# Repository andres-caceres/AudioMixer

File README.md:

# AudioMixer v1.2 (beta)
Digital audio USB controller firmware for Windows, tested using an Arduino Nano. Lets you control the volume of different applications using potentiometers and mute each channel individually using push button switches.
Based on [Deej by Omriharel], can be used with deej.exe Windows client.

## Features
* Includes mute push button functionality and ADC range calibration settings for each channel.
* Supports TM1637 7 segment display for controller position feedback.
* Supports LED push buttons for visual feedback.
* Uses digital filtering to increase potentiometer position accuracy.

## Upcoming (desired) Features
* Windows audio device selection using one push button press.
* Push buttons that can be used for executing Macros to automate tasks.
* Calibration subroutine for sliders

(Work in progress)

[//]: #

[Deej by Omriharel]: <https://github.com/omriharel/deej>

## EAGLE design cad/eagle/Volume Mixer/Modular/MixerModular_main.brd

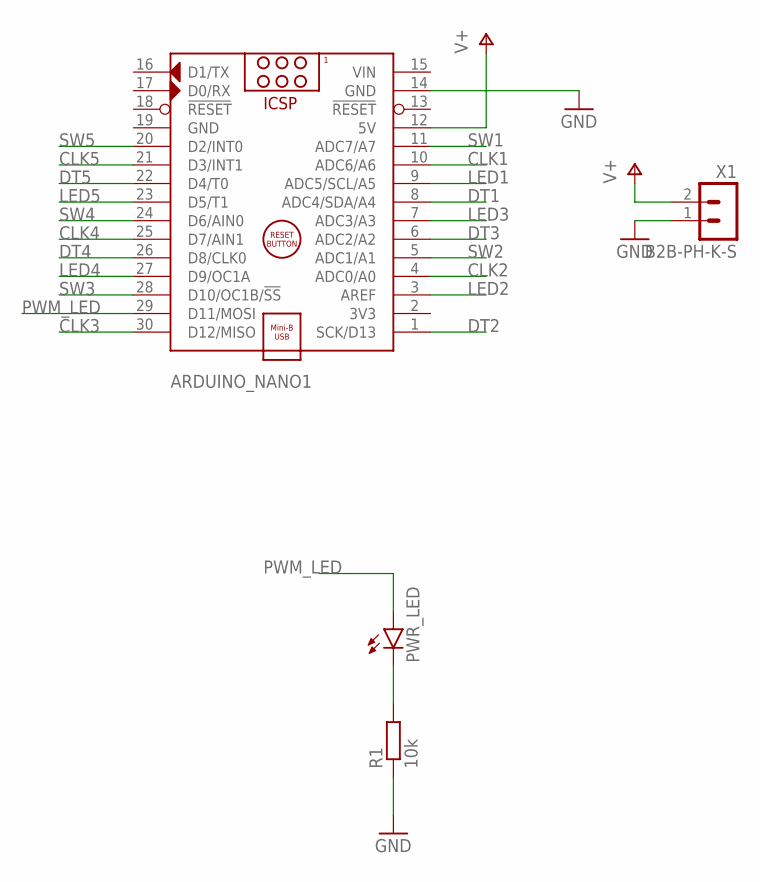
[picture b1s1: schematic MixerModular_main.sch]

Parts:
ARDUINO_NANO1: ARDUINO_NANO
PWR_LED: LED5MM
R1: 10k; 0207/10
X1: B2B-PH-K-S

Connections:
CLK1: ARDUINO_NANO1.10 (ADC6/A6)
CLK2: ARDUINO_NANO1.4 (ADC0/A0)
CLK3: ARDUINO_NANO1.30 (D12/MISO)
CLK4: ARDUINO_NANO1.25 (D7/AIN1)
CLK5: ARDUINO_NANO1.21 (D3/INT1)
DT1: ARDUINO_NANO1.8 (ADC4/SDA/A4)
DT2: ARDUINO_NANO1.1 (SCK/D13)
DT3: ARDUINO_NANO1.6 (ADC2/A2)
DT4: ARDUINO_NANO1.26 (D8/CLK0)
DT5: ARDUINO_NANO1.22 (D4/T0)
GND: ARDUINO_NANO1.14 (GND), ARDUINO_NANO1.19 (GND), R1.1, X1.1
LED1: ARDUINO_NANO1.9 (ADC5/SCL/A5)
LED2: ARDUINO_NANO1.3 (AREF)
LED3: ARDUINO_NANO1.7 (ADC3/A3)
LED4: ARDUINO_NANO1.27 (D9/OC1A)
LED5: ARDUINO_NANO1.23 (D5/T1)
unnamed: PWR_LED.K (C), R1.2
PWM_LED: ARDUINO_NANO1.29 (D11/MOSI), PWR_LED.A
SW1: ARDUINO_NANO1.11 (ADC7/A7)
SW2: ARDUINO_NANO1.5 (ADC1/A1)
SW3: ARDUINO_NANO1.28 (D10/OC1B/!SS)
SW4: ARDUINO_NANO1.24 (D6/AIN0)
SW5: ARDUINO_NANO1.20 (D2/INT0)
V+: ARDUINO_NANO1.12 (5V), X1.2
VIN: ARDUINO_NANO1.15 (VIN)

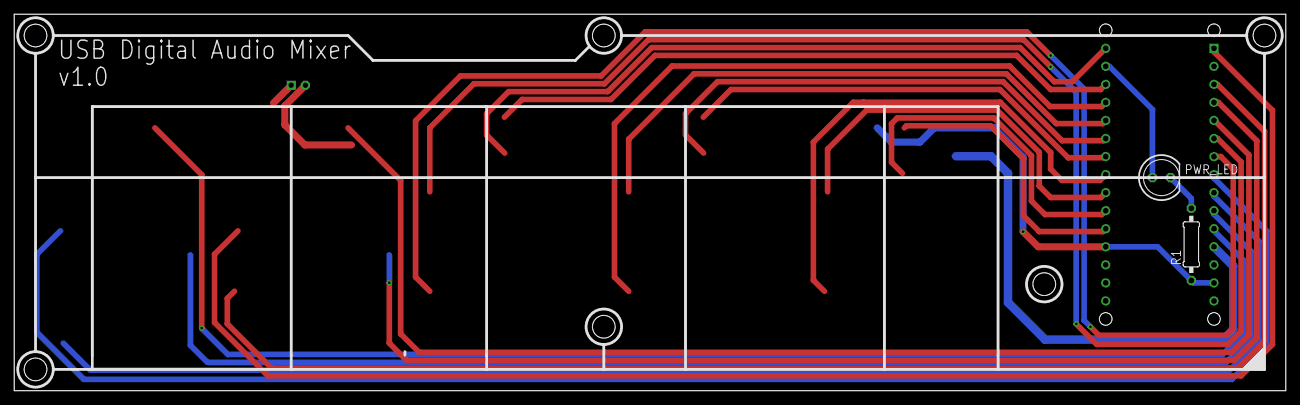
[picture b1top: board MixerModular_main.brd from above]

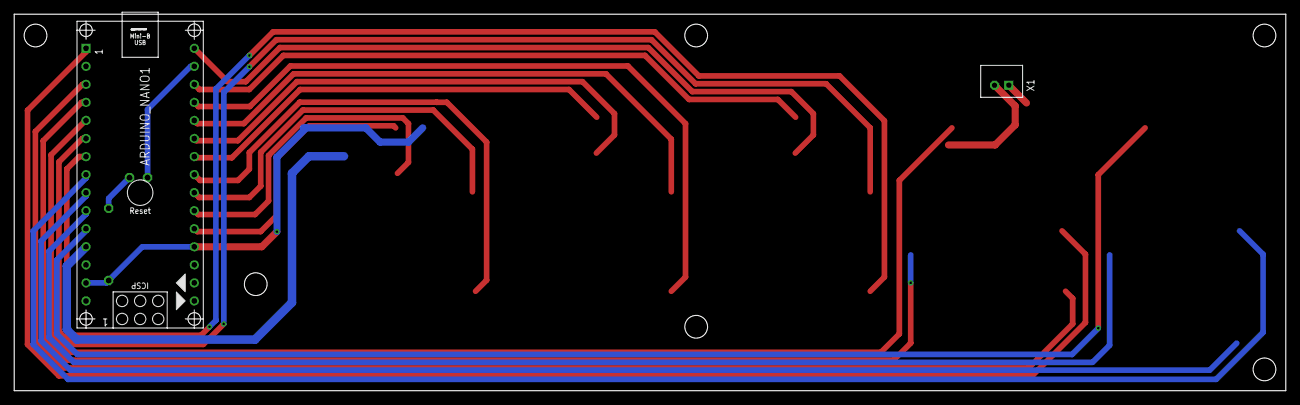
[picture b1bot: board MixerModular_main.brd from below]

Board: 2 copper layers, 179.0 x 53.0 mm, 4 parts (2 on the bottom side), 4 nets.

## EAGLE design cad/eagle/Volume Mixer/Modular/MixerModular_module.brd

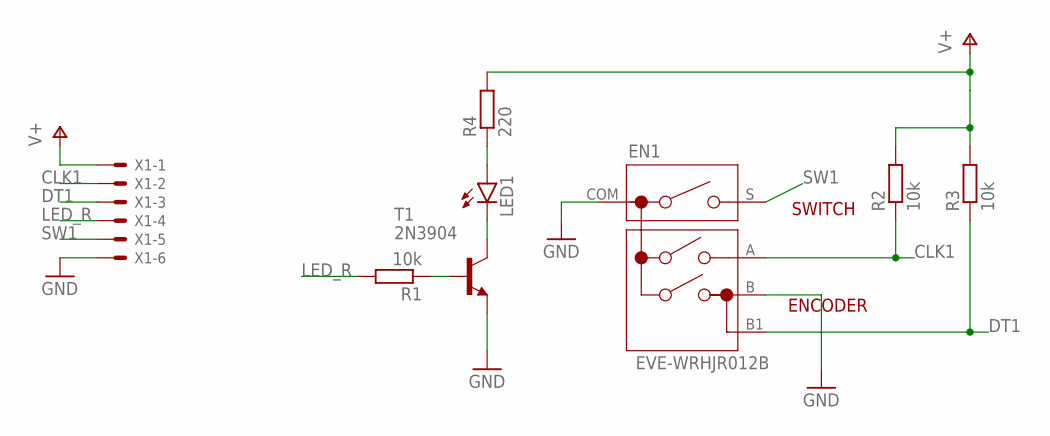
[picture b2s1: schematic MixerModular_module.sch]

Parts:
EN1: EVE-WRHJR012B
LED1: LED5MM
R1, R2, R3: 10k; 0207/10
R4: 220; 0207/10
T1: 2N3904; TO92
X1: 22-23-2061

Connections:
CLK1: EN1.A, R2.1, X1.2
DT1: EN1.B1, R3.1, X1.3
GND: EN1.B, EN1.COM, T1.3 (E), X1.6
LED_R: R1.2, X1.4
unnamed: LED1.A, R4.1
unnamed: R1.1, T1.2 (B)
unnamed: LED1.K (C), T1.1 (C)
SW1: EN1.S, X1.5
V+: R2.2, R3.2, R4.2, X1.1

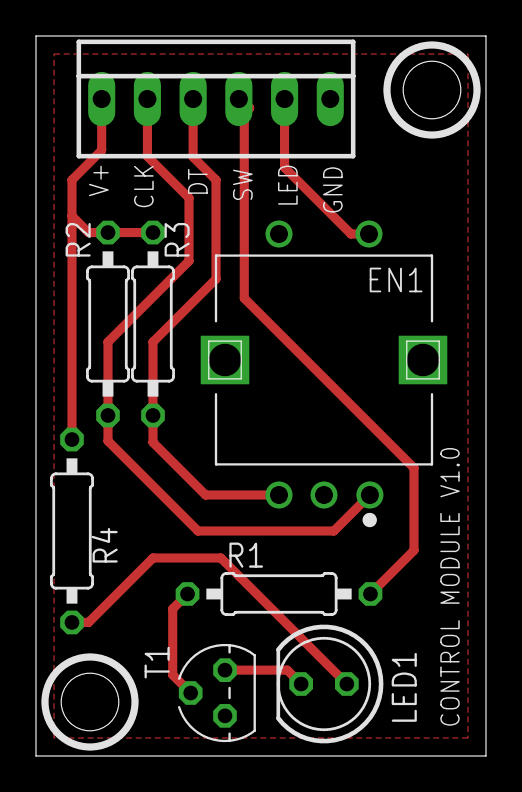
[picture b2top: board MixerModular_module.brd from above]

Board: 2 copper layers, 25.0 x 40.0 mm, 8 parts (0 on the bottom side), 9 nets.

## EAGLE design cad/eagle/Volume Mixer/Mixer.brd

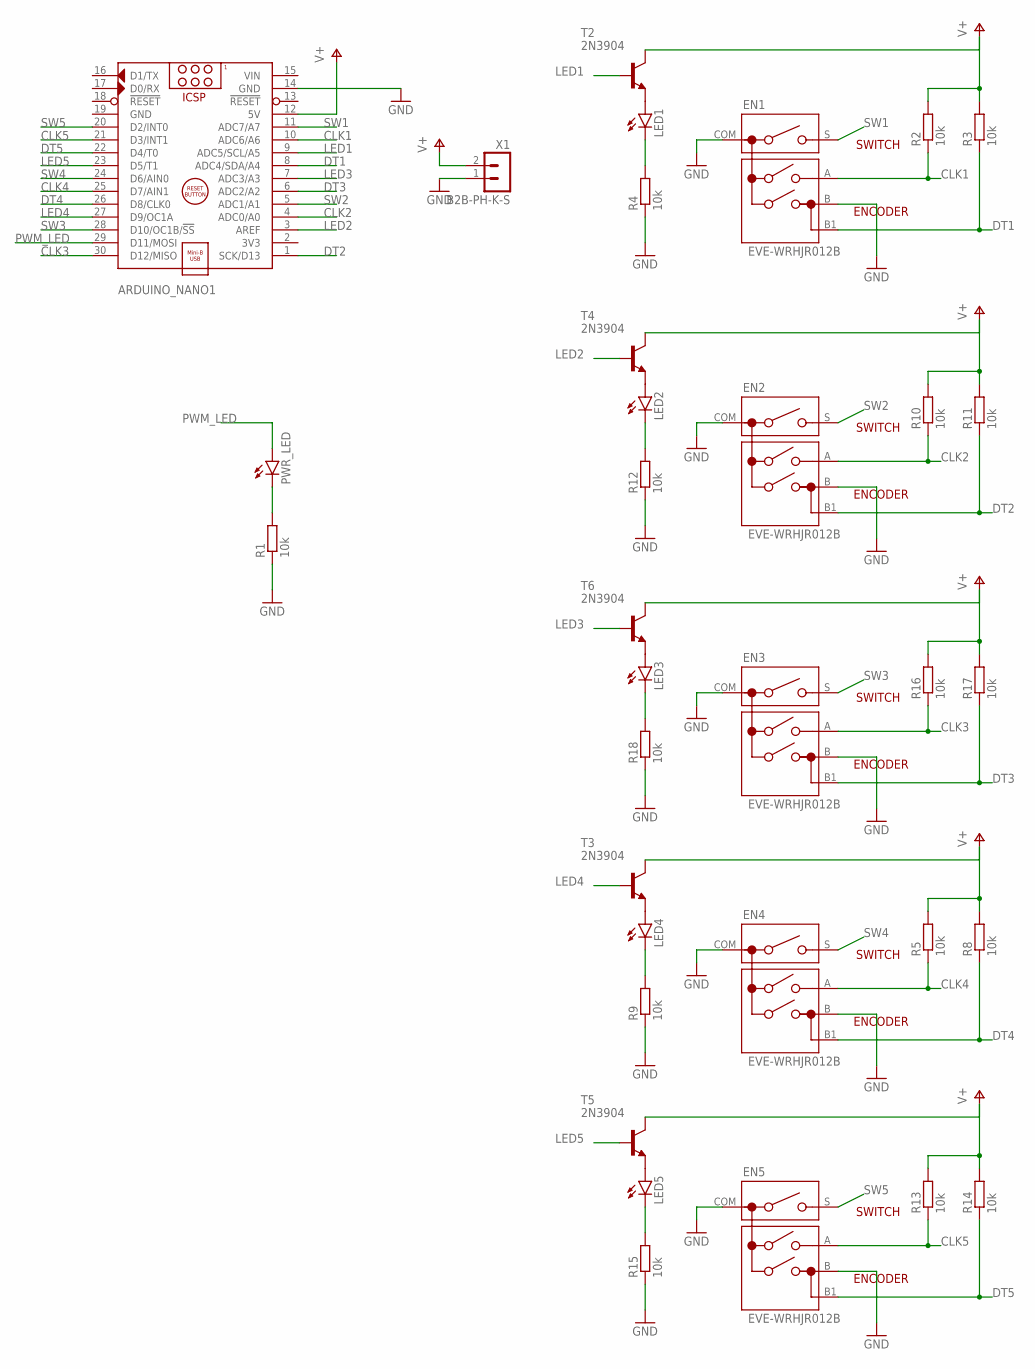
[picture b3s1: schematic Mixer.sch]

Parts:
ARDUINO_NANO1: ARDUINO_NANO
EN1, EN2, EN3, EN4, EN5: EVE-WRHJR012B
LED1, LED2, LED3, LED4, LED5: LED5MM
PWR_LED: LED5MM
R1, R2, R3, R4, R5, R8, R9, R10, R11, R12, R13, R14, R15, R16, R17, R18: 10k; 0207/10
T2, T3, T4, T5, T6: 2N3904; TO92
X1: B2B-PH-K-S

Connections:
CLK1: ARDUINO_NANO1.10 (ADC6/A6), EN1.A, R2.1
CLK2: ARDUINO_NANO1.4 (ADC0/A0), EN2.A, R10.1
CLK3: ARDUINO_NANO1.30 (D12/MISO), EN3.A, R16.1
CLK4: ARDUINO_NANO1.25 (D7/AIN1), EN4.A, R5.1
CLK5: ARDUINO_NANO1.21 (D3/INT1), EN5.A, R13.1
DT1: ARDUINO_NANO1.8 (ADC4/SDA/A4), EN1.B1, R3.1
DT2: ARDUINO_NANO1.1 (SCK/D13), EN2.B1, R11.1
DT3: ARDUINO_NANO1.6 (ADC2/A2), EN3.B1, R17.1
DT4: ARDUINO_NANO1.26 (D8/CLK0), EN4.B1, R8.1
DT5: ARDUINO_NANO1.22 (D4/T0), EN5.B1, R14.1
GND: ARDUINO_NANO1.14 (GND), ARDUINO_NANO1.19 (GND), EN1.B, EN1.COM, EN2.B, EN2.COM, EN3.B, EN3.COM, EN4.B, EN4.COM, EN5.B, EN5.COM, R1.1, R4.1, R9.1, R12.1, R15.1, R18.1, X1.1
LED1: ARDUINO_NANO1.9 (ADC5/SCL/A5), T2.2 (B)
LED2: ARDUINO_NANO1.3 (AREF), T4.2 (B)
LED3: ARDUINO_NANO1.7 (ADC3/A3), T6.2 (B)
LED4: ARDUINO_NANO1.27 (D9/OC1A), T3.2 (B)
LED5: ARDUINO_NANO1.23 (D5/T1), T5.2 (B)
unnamed: PWR_LED.K (C), R1.2
unnamed: LED1.K (C), R4.2
unnamed: LED1.A, T2.3 (E)
unnamed: LED4.K (C), R9.2
unnamed: LED4.A, T3.3 (E)
unnamed: LED2.K (C), R12.2
unnamed: LED2.A, T4.3 (E)
unnamed: LED5.K (C), R15.2
unnamed: LED5.A, T5.3 (E)
unnamed: LED3.K (C), R18.2
unnamed: LED3.A, T6.3 (E)
PWM_LED: ARDUINO_NANO1.29 (D11/MOSI), PWR_LED.A
SW1: ARDUINO_NANO1.11 (ADC7/A7), EN1.S
SW2: ARDUINO_NANO1.5 (ADC1/A1), EN2.S
SW3: ARDUINO_NANO1.28 (D10/OC1B/!SS), EN3.S
SW4: ARDUINO_NANO1.24 (D6/AIN0), EN4.S
SW5: ARDUINO_NANO1.20 (D2/INT0), EN5.S
V+: ARDUINO_NANO1.12 (5V), R2.2, R3.2, R5.2, R8.2, R10.2, R11.2, R13.2, R14.2, R16.2, R17.2, T2.1 (C), T3.1 (C), T4.1 (C), T5.1 (C), T6.1 (C), X1.2
VIN: ARDUINO_NANO1.15 (VIN)

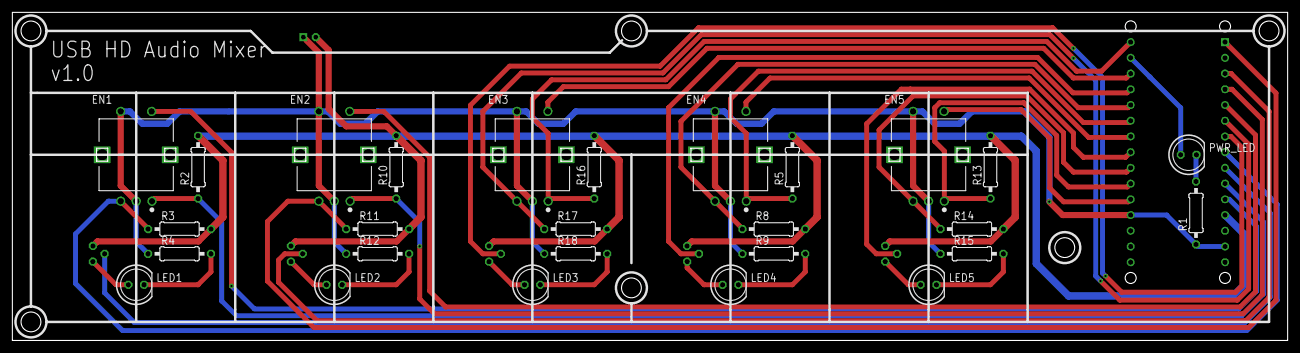
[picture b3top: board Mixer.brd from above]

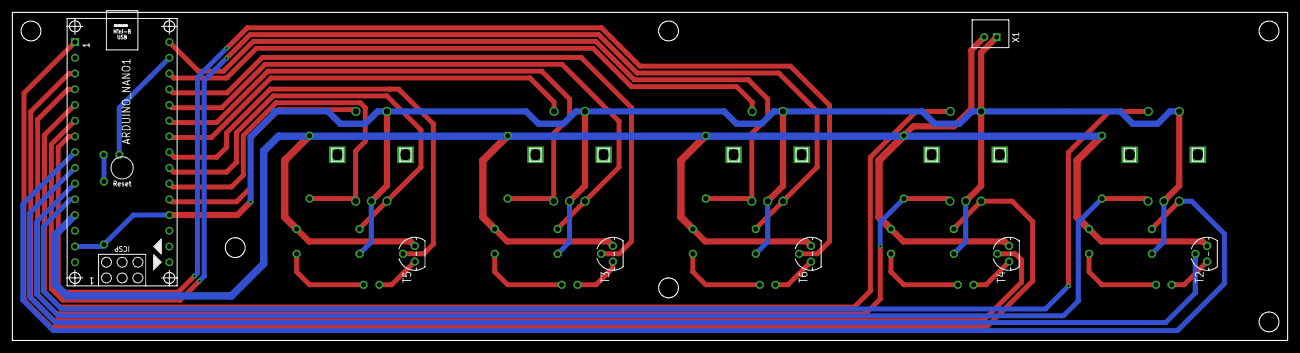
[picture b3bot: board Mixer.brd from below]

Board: 2 copper layers, 206.0 x 53.0 mm, 34 parts (7 on the bottom side), 34 nets.

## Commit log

2022-01-28 primer commit
2022-01-28 reordenar + readme
2023-03-30 v0.1 for testing
2023-03-30 fixed typos in README.md
2023-04-06 v1.1 fixed issues
2023-04-07 startup sequence display animation, IIR filter tuning
2023-05-30 now slider value calibration is done at ADC reading level instead of the lcd display
2023-07-27 toggle button first commit
